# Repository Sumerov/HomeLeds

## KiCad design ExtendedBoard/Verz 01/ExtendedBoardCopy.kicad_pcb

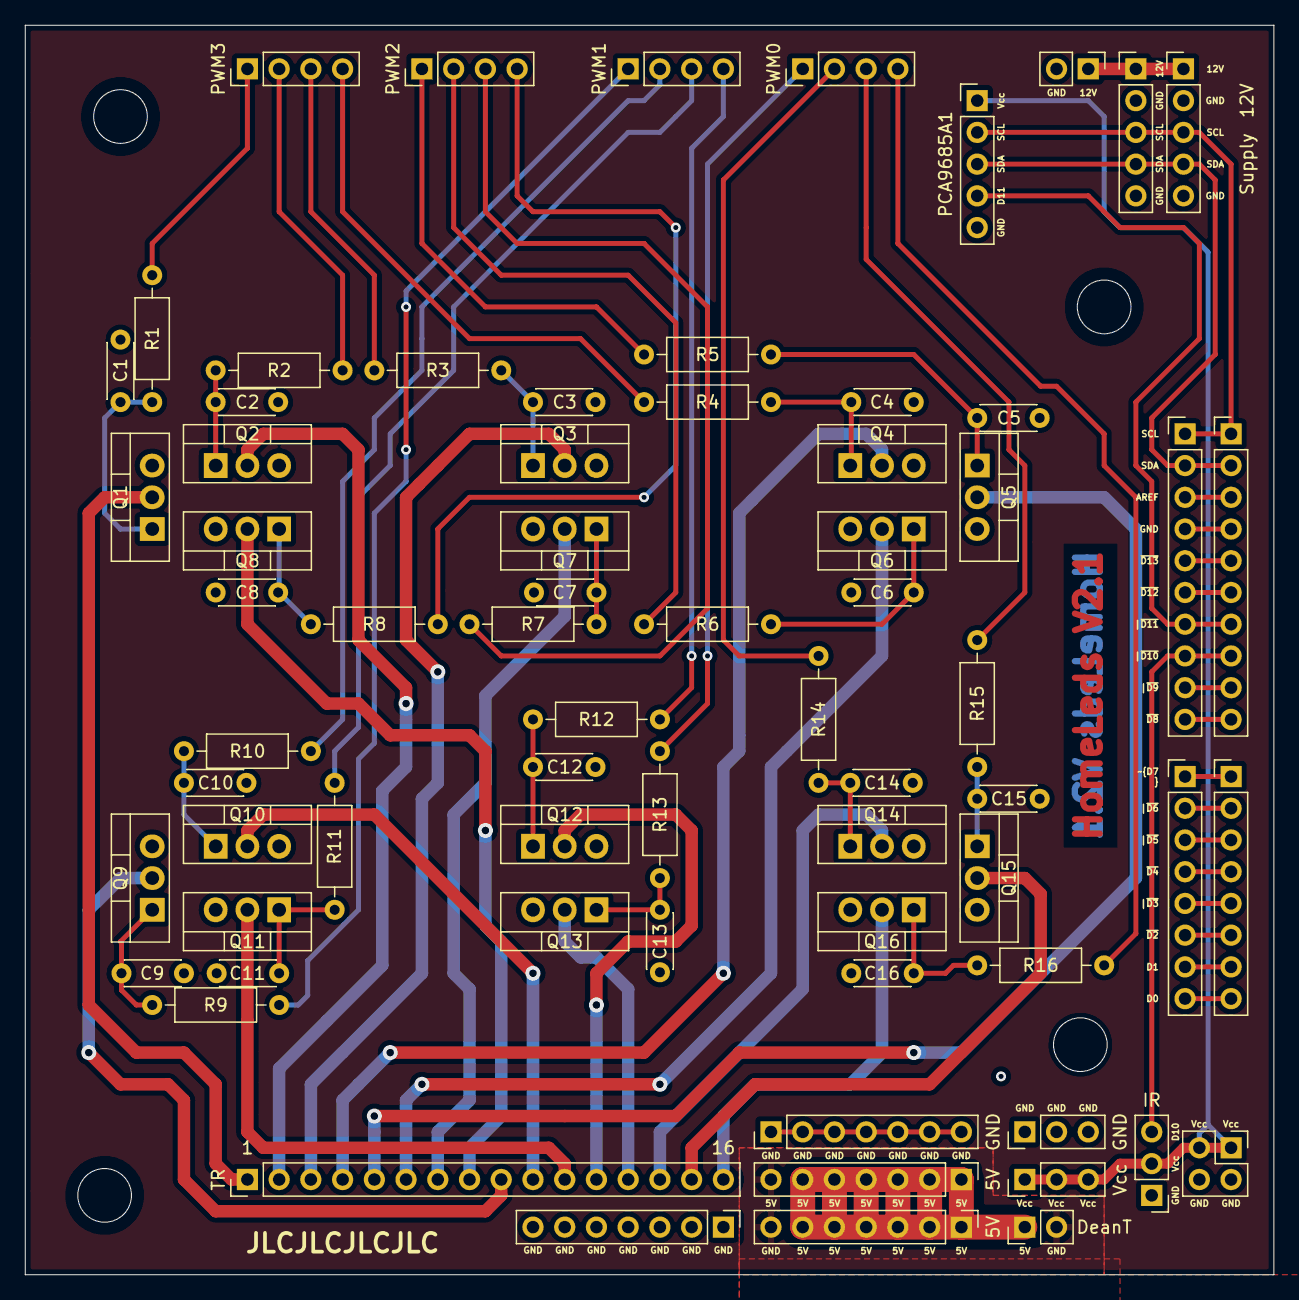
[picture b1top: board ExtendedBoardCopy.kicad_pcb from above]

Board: 2 copper layers, 99.9 x 100.0 mm, 74 parts (0 on the bottom side), 69 nets.

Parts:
5V, 5V#2: SUP ++; PinHeader_1x07_P2.54mm_Vertical
12V: INPUTS_Ard02; PinHeader_1x05_P2.54mm_Vertical
+12V: 12VOutput; PinHeader_1x02_P2.54mm_Vertical
C1, C2, C3, C4, C5, C6, C7, C8, C9, C10, C11, C12, C13, C14, C15, C16: 100n; C_Disc_D4.3mm_W1.9mm_P5.00mm
DH1, DH2, DH2#2, DH3: MountingHole_4.3mm_M4
DeanT: DeanTInput_01; PinHeader_1x02_P2.54mm_Vertical
GND: PINOUT GNDS; PinHeader_1x07_P2.54mm_Vertical
GND#2: PINOUT GNDS; PinHeader_1x07_P2.54mm_Vertical
GND#3: PINOUT GNDs; PinHeader_1x03_P2.54mm_Vertical
IR: PINOUT IR; PinHeader_1x03_P2.54mm_Vertical
J5: Ard 01; PinHeader_1x10_P2.54mm_Vertical
J6: Ard 02; PinHeader_1x08_P2.54mm_Vertical
J7: Ard 02_1; PinHeader_1x08_P2.54mm_Vertical
J7#2: Ard 01_1; PinHeader_1x10_P2.54mm_Vertical
PCA9685A1: Inputs_PCA9685A; PinHeader_1x05_P2.54mm_Vertical
PWM0: PWMpair4; PinHeader_1x04_P2.54mm_Vertical
PWM1: PWMpair3; PinHeader_1x04_P2.54mm_Vertical
PWM2: PWMpair2; PinHeader_1x04_P2.54mm_Vertical
PWM3: PWMpair1; PinHeader_1x04_P2.54mm_Vertical
Q1, Q2, Q3, Q4, Q5, Q6, Q7, Q8, Q9, Q10, Q11, Q12, Q13, Q14, Q15, Q16: TIP120; TO-220-3_Vertical
R1, R2, R3, R4, R5, R6, R7, R8, R9, R10, R11, R12, R13, R14, R15, R16: 3k3; R_Axial_DIN0207_L6.3mm_D2.5mm_P10.16mm_Horizontal
SUPPLY ARD: SUPPLYard; PinHeader_2x02_P2.54mm_Vertical
Supply: INPUTS_Ard02_01; PinHeader_1x05_P2.54mm_Vertical
TR: RGB pinout; PinHeader_1x16_P2.54mm_Vertical
Vcc: PINOUT ard Supply; PinHeader_1x03_P2.54mm_Vertical

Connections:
5V+: 5V.1, 5V.2, 5V.3, 5V.4, 5V.5, 5V.6, 5V#2.1, 5V#2.2, 5V#2.3, 5V#2.4, 5V#2.5, 5V#2.6, DeanT.1
12V+: 12V.1, +12V.1, Supply.1
AREF: J5.3, J7#2.3
D01: PWM3.1, R1.1
D02: PWM3.2, R2.1
D03: PWM3.3, R3.1
D04: PWM3.4, R4.1
D05: PWM2.1, R5.1
D06: PWM2.2, R6.1
D07: PWM2.3, R7.1
D08: PWM2.4, R8.1
D09: PWM1.1, R9.1
D10: PWM1.2, R10.1
D11: PWM1.3, R11.1
D12: PWM1.4, R12.1
D13: PWM0.1, R13.1
D14: PWM0.2, R14.1
D15: PWM0.3, R15.1
D16: PWM0.4, R16.1
DI0: J6.8, J7.8
DI1: J6.7, J7.7
DI2: J6.6, J7.6
DI3: J6.5, J7.5
DI4: J6.4, J7.4
DI5: J6.3, J7.3
DI6: J6.2, J7.2
DI7: J6.1, J7.1
DI8: J5.10, J7#2.10
DI9: J5.9, J7#2.9
DI10: IR.3, J5.8, J7#2.8
DI11: J5.7, J7#2.7, PCA9685A1.4
DI12: J5.6, J7#2.6
DI13: J5.5, J7#2.5
GND: 5V.7, 5V#2.7, 12V.2, +12V.2, C1.2, C2.2, C3.2, C4.2, C5.2, C6.2, C7.2, C8.2, C9.2, C10.2, C11.2, C12.2, C13.2, C14.2, C15.2, C16.2, DeanT.2, GND#2.1, GND#2.2, GND#2.3, GND#2.4, GND#2.5, GND#2.6, GND#2.7, GND#3.1, GND#3.2, GND#3.3, IR.1, J5.4, J7#2.4, PCA9685A1.5, Q1.3, Q2.3, Q3.3, Q4.3, Q5.3, Q6.3, Q7.3, Q8.3, Q9.3, Q10.3, Q11.3, Q12.3, Q13.3, Q14.3, Q15.3, Q16.3, SUPPLY ARD.2, SUPPLY ARD.4, Supply.2
LED01: Q1.2, TR.1
LED02: Q2.2, TR.2
LED03: Q3.2, TR.3
LED04: Q4.2, TR.4
LED05: Q5.2, TR.5
LED06: Q6.2, TR.6
LED07: Q7.2, TR.7
LED08: Q8.2, TR.8
LED09: Q9.2, TR.9
LED10: Q10.2, TR.10
LED11: Q11.2, TR.11
LED12: Q12.2, TR.12
LED13: Q13.2, TR.13
LED14: Q14.2, TR.14
LED15: Q15.2, TR.15
LED16: Q16.2, TR.16
unnamed: C1.1, Q1.1, R1.2
unnamed: C2.1, Q2.1, R2.2
unnamed: C3.1, Q3.1, R3.2
unnamed: C4.1, Q4.1, R4.2
unnamed: C5.1, Q5.1, R5.2
unnamed: C6.1, Q6.1, R6.2
unnamed: C7.1, Q7.1, R7.2
unnamed: C8.1, Q8.1, R8.2
unnamed: C9.1, Q9.1, R9.2
unnamed: C10.1, Q10.1, R10.2
unnamed: C11.1, Q11.1, R11.2
unnamed: C12.1, Q12.1, R12.2
unnamed: C13.1, Q13.1, R13.2
unnamed: C14.1, Q14.1, R14.2
unnamed: C15.1, Q15.1, R15.2
unnamed: C16.1, Q16.1, R16.2
SCL1: 12V.3, J5.1, J7#2.1, PCA9685A1.2, Supply.3
SDA1: 12V.4, J5.2, J7#2.2, PCA9685A1.3, Supply.4
Vcc: IR.2, PCA9685A1.1, SUPPLY ARD.1, SUPPLY ARD.3, Vcc.1, Vcc.2, Vcc.3

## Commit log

2020-03-17 Upload 00
2020-03-17 SaveStatus
2020-07-22 Upravena Welcome animace. Upraven LCD output
2020-07-22 Uprava LCD, nahrani
2020-07-26 Maping stareho i noveho ovladace, intro edited (no shits now)
2020-09-03 project structure change
2020-09-03 Design save
2020-09-22 zaloha pcb
2020-09-23 zaloha, verze 1 PCB
2020-09-23 zaloha verze 1
2020-10-07 zaloha
2023-01-19 Zaloha 19.01.2023
2023-01-21 no message
2023-08-15 backup
2023-09-12 oprava chyb
